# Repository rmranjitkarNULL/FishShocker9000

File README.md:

# FishShocker9000
A hardware/software system for high-voltage pulse generation and control, integrating custom PCB design, embedded firmware, and testing tools.

---

## Overview
FishShocker9000 was developed as a project to explore **embedded systems design, PCB layout, and high-voltage electronics**.  
The system combines custom hardware with **C/C++ firmware** to generate controlled electrical pulses, managed through a modular and extensible software stack.

---

## Hardware
- **Custom PCB Design** (schematics + board layouts)  
- Power delivery circuits for safe and reliable pulse generation  
- Signal conditioning and protection hardware  
- Mixed-signal layout considerations for high-voltage operation  

---

## Features
- Precise pulse generation and control  
- Configurable timing and waveform parameters  
- Modular design for hardware/firmware scalability  
- PCB + firmware tightly integrated for performance and safety  

---

## Repository Structure
FishShocker9000/
├── include/ # Header files
├── lib/ # Custom libraries
├── src/ # Firmware source code
├── test/ # Testing and validation scripts
├── pcb/ # PCB design files (schematics, layouts)
└── README.md # Project documentation

---

## Future Improvements
- Improve PCB design for efficiency and miniaturization  
- Expand safety features and protection circuitry  

---

TODO
-[ ] Redo Readme
-[ ] Make assembly guide
-[ ] [add](https://www.pjrc.com/teensy/loader.html)

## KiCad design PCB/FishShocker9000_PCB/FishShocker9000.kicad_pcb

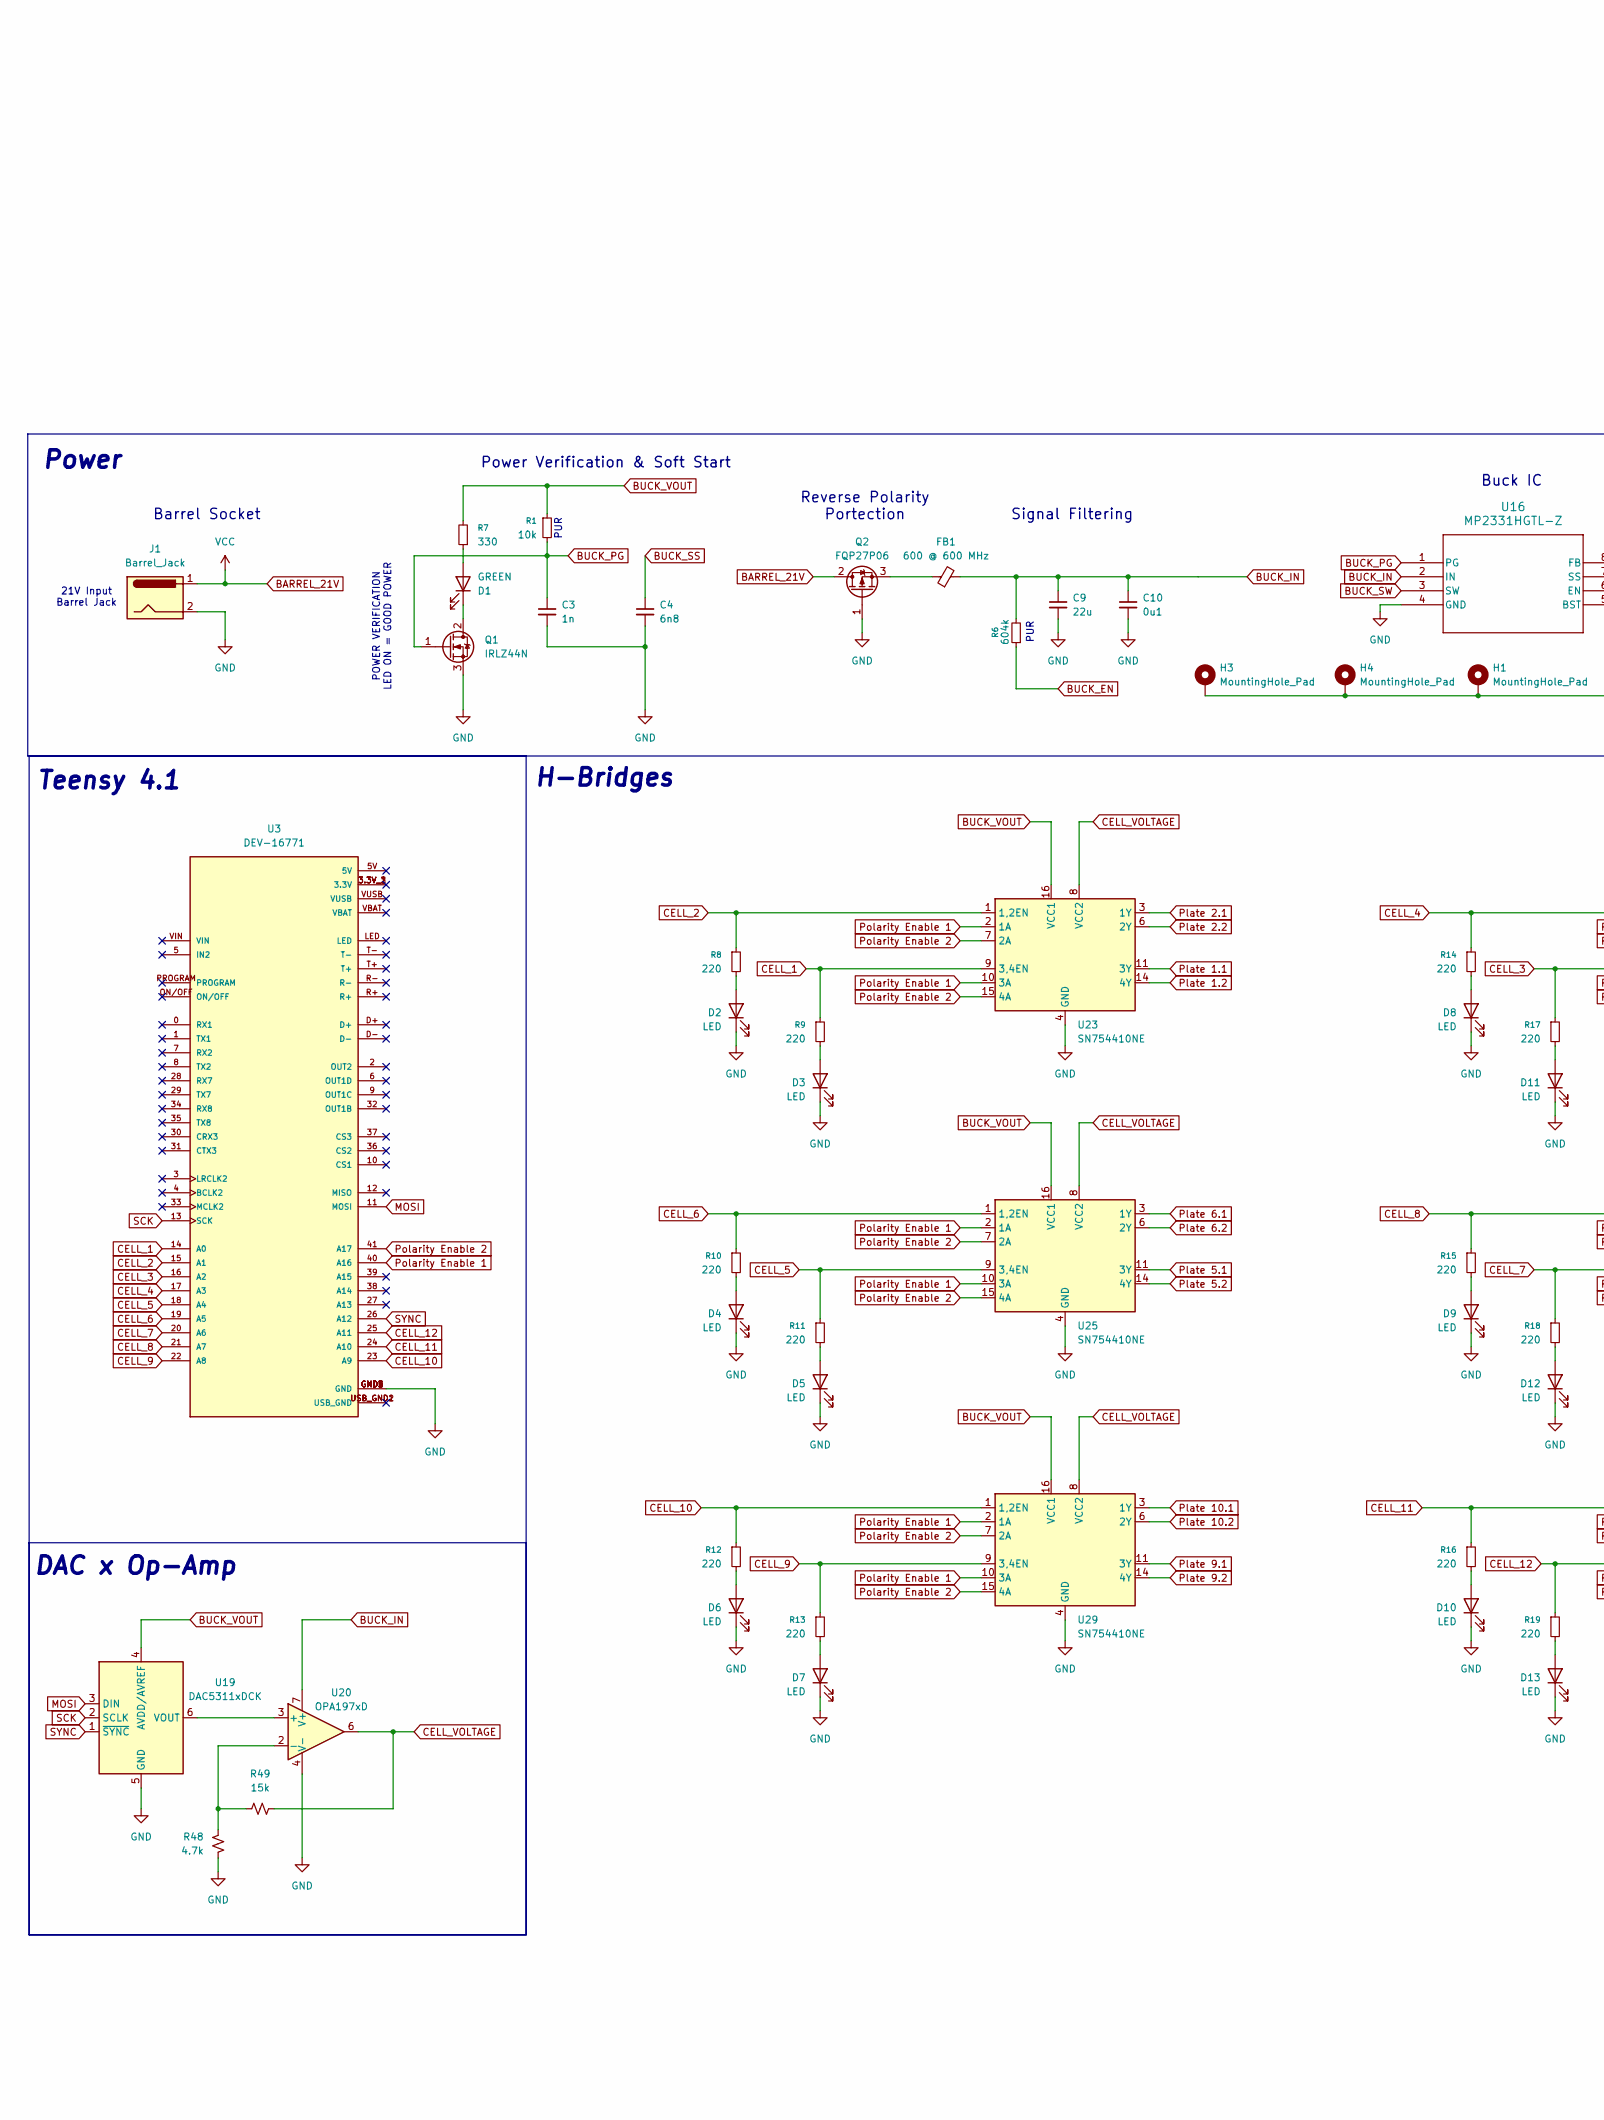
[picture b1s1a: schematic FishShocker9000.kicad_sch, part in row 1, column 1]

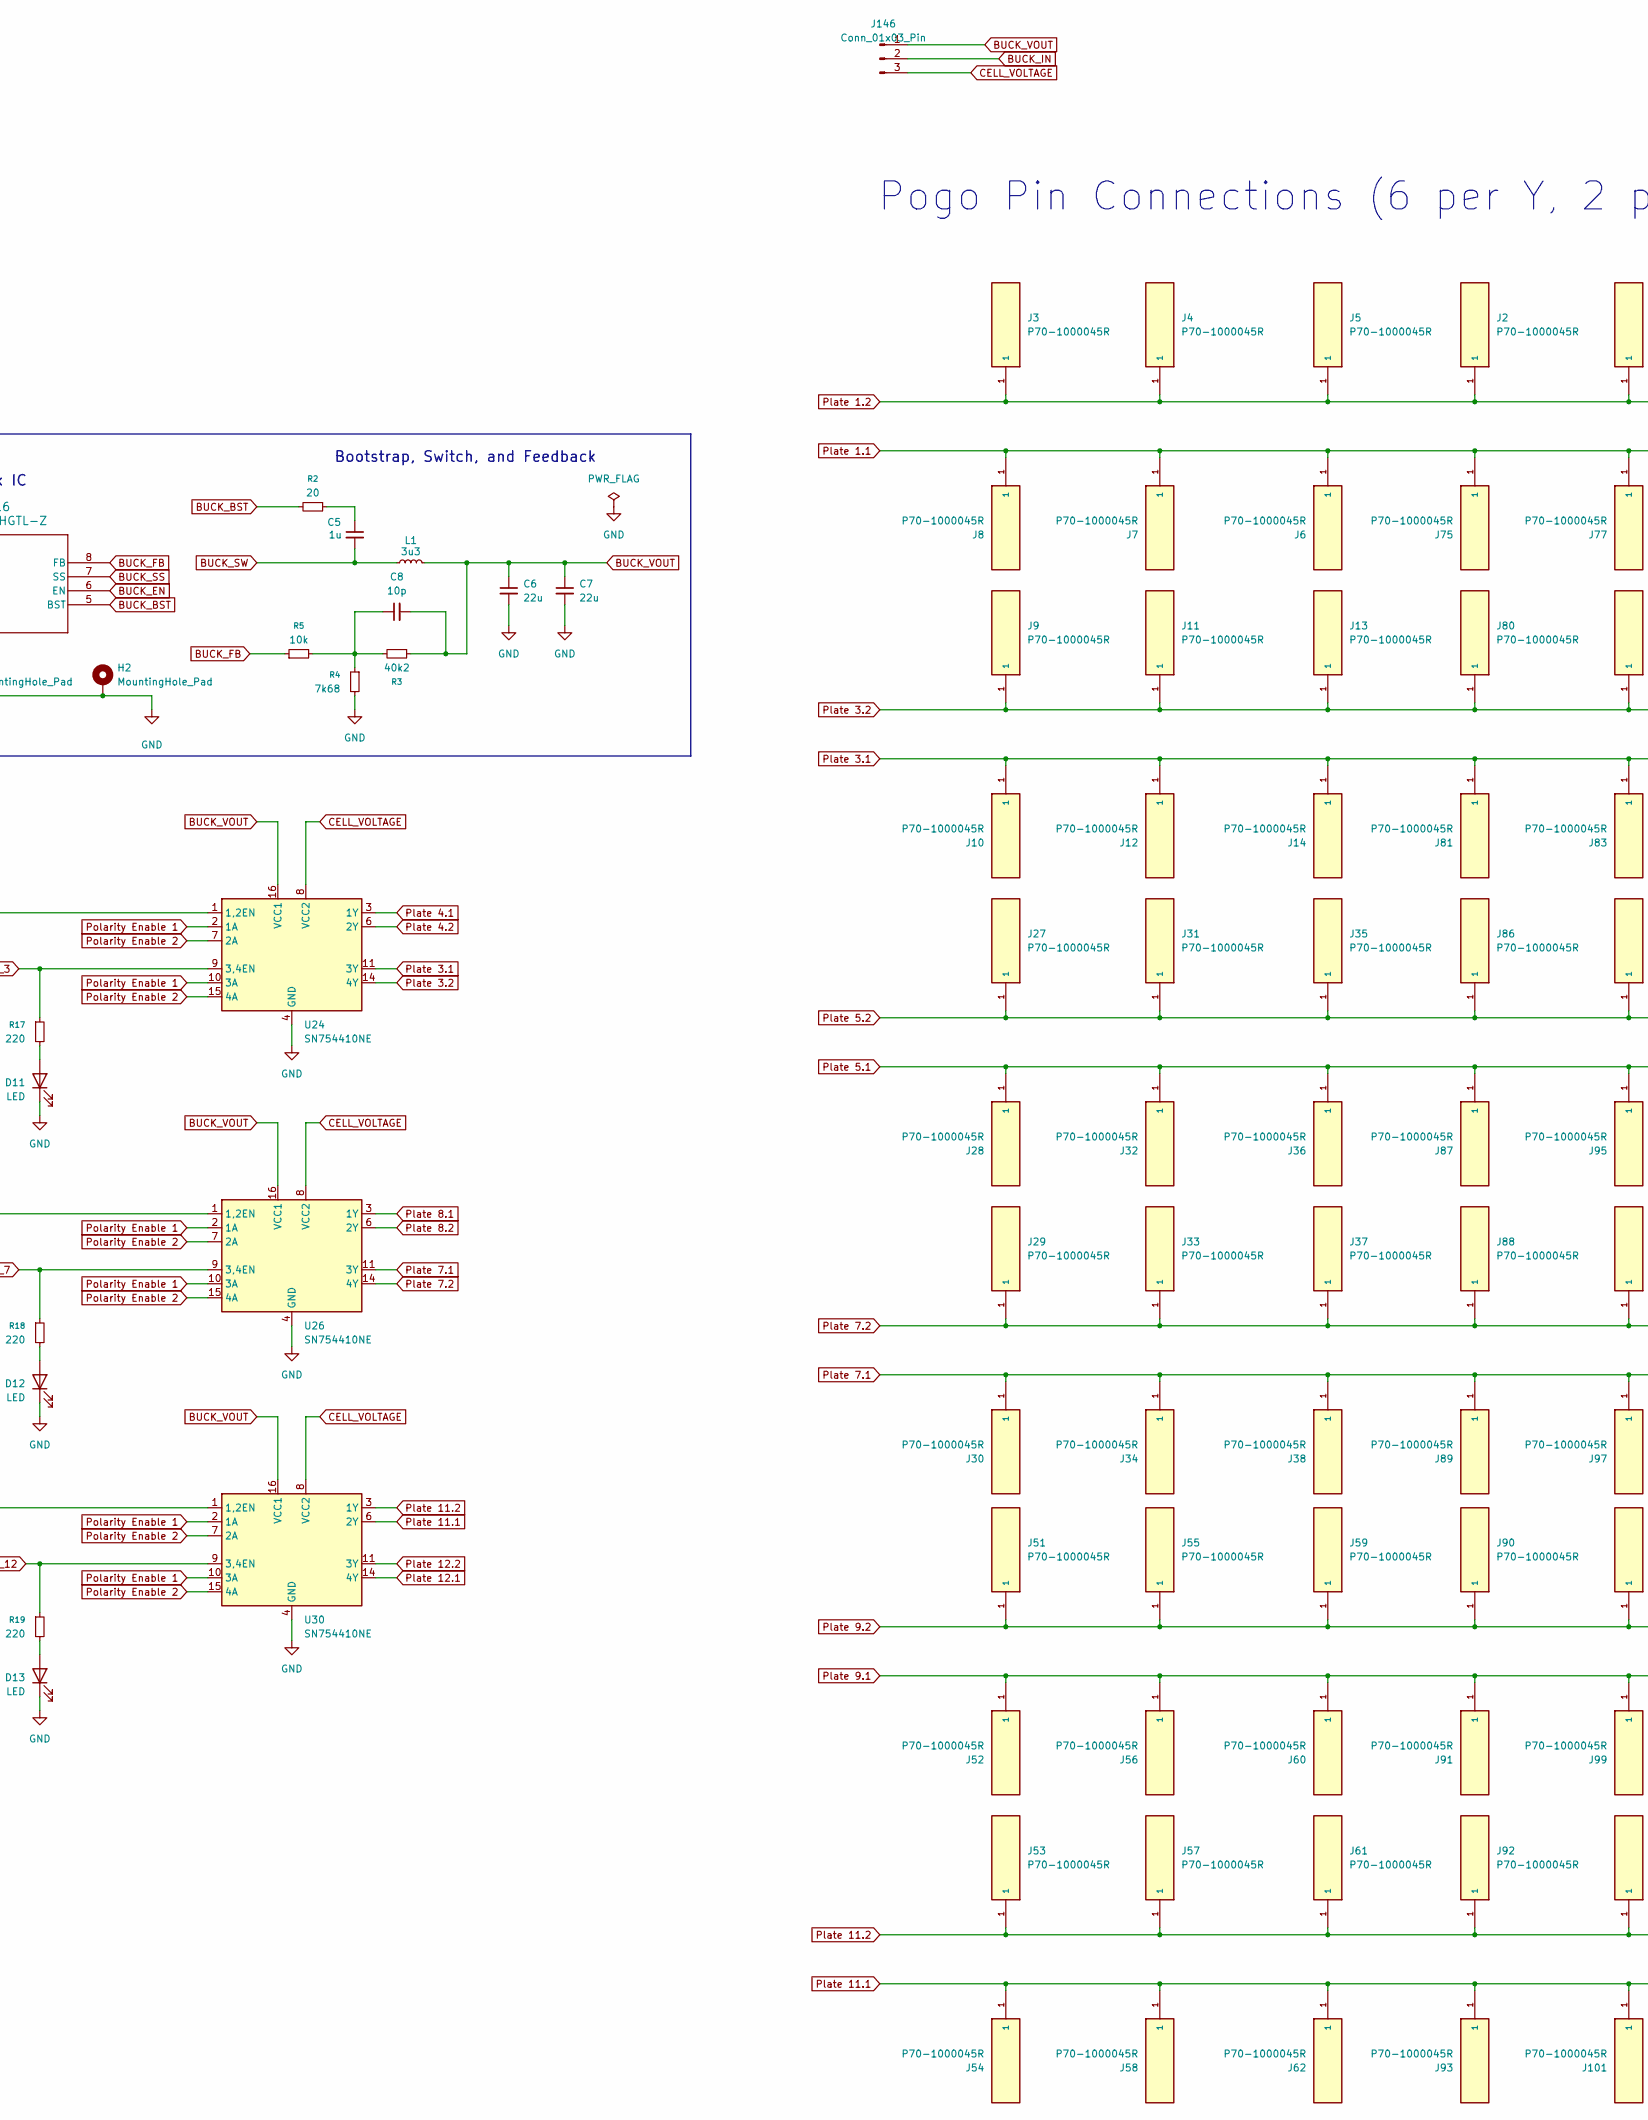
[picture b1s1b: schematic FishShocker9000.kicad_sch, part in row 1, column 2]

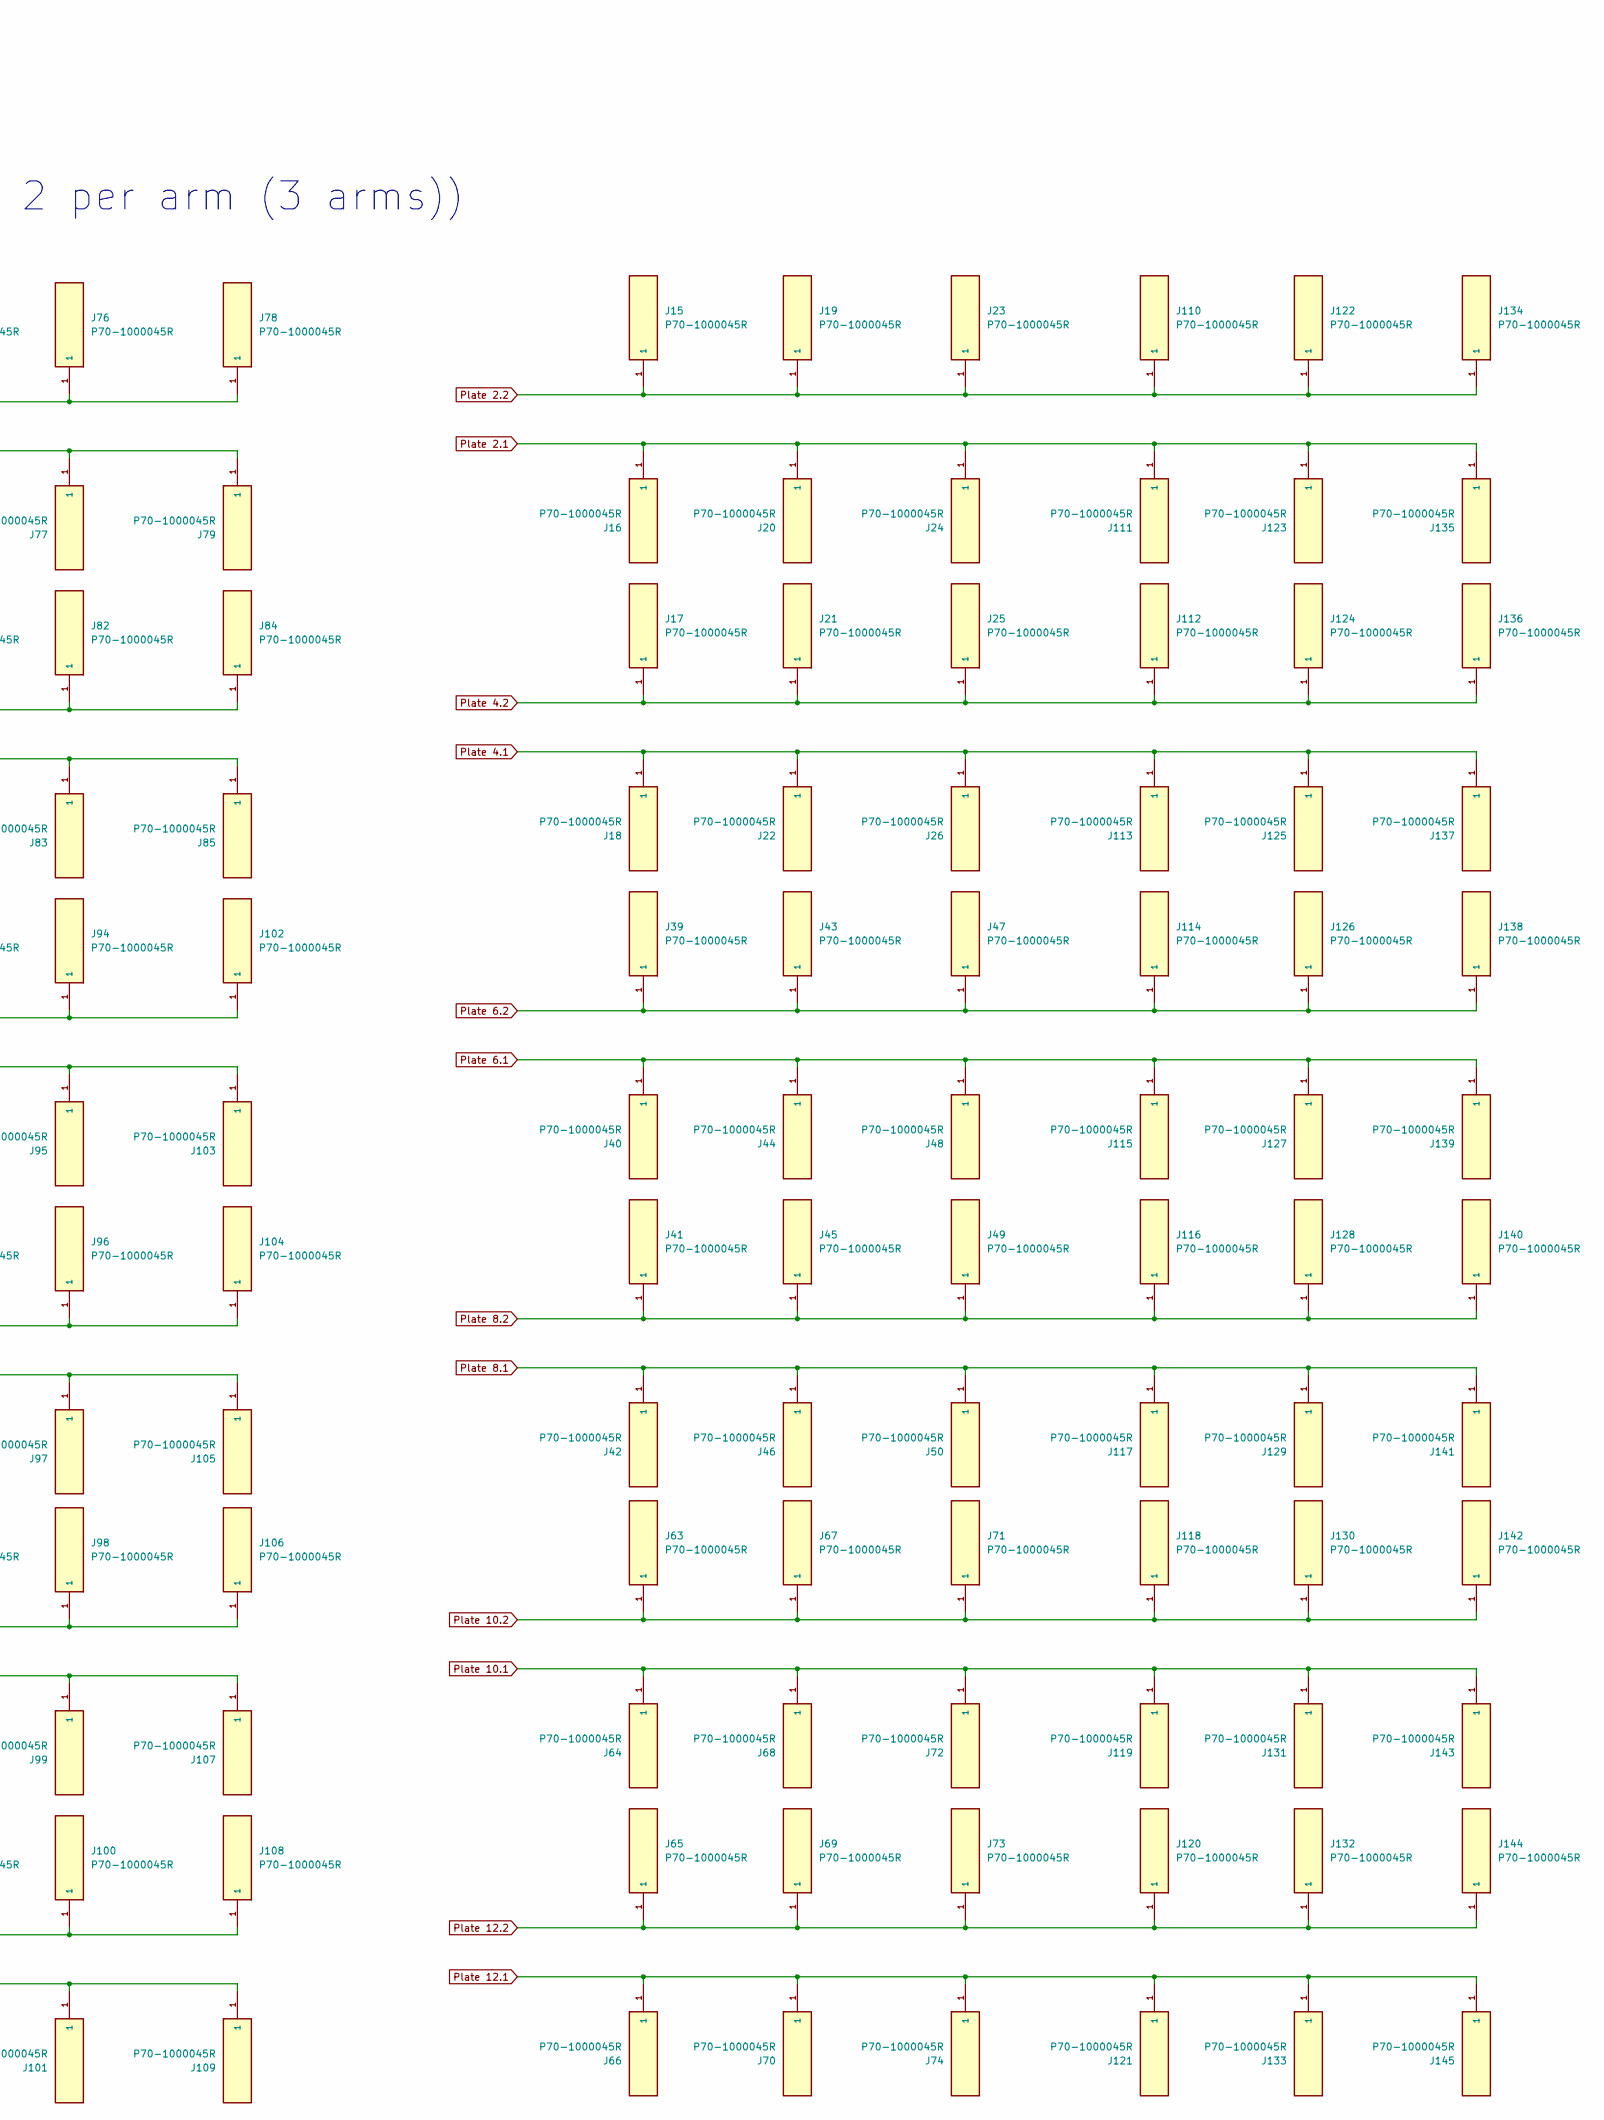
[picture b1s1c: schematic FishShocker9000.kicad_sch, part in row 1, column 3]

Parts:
C3: 1n; C_0402_1005Metric
C4: 6n8; C_0603_1608Metric
C5: 1u; C_1206_3216Metric
C6, C7, C9: 22u; C_1206_3216Metric
C8: 10p; C_0603_1608Metric
C10: 0u1; C_0603_1608Metric
D1: GREEN; LED_0805_2012Metric
D2, D3, D4, D5, D6, D7, D8, D9, D10, D11, D12, D13: LED; LED_0805_2012Metric
FB1: 600 @ 600 MHz; L_0805_2012Metric
H1, H2, H3, H4: MountingHole_Pad; MountingHole_2.2mm_M2_DIN965_Pad
J1: Barrel_Jack; BarrelJack_CLIFF_FC681465S_SMT_Horizontal
J2, J3, J4, J5, J6, J7, J8, J9, J10, J11, J12, J13, J14, J15, J16, J17, J18, J19, J20, J21, J22, J23, J24, J25, J26, J27, J28, J29, J30, J31, J32, J33, J34, J35, J36, J37, J38, J39, J40, J41, J42, J43, J44, J45, J46, J47, J48, J49, J50, J51, J52, J53, J54, J55, J56, J57, J58, J59, J60, J61, J62, J63, J64, J65, J66, J67, J68, J69, J70, J71, J72, J73, J74, J75, J76, J77, J78, J79, J80, J81, J82, J83, J84, J85, J86, J87, J88, J89, J90, J91, J92, J93, J94, J95, J96, J97, J98, J99, J100, J101, J102, J103, J104, J105, J106, J107, J108, J109, J110, J111, J112, J113, J114, J115, J116, J117, J118, J119, J120, J121, J122, J123, J124, J125, J126, J127, J128, J129, J130, J131, J132, J133, J134, J135, J136, J137, J138, J139, J140, J141, J142, J143, J144, J145: P70-1000045R; PinHeader_1x01_P2.54mm_Vertical; PARTREV 4
J146: Conn_01x03_Pin; PinHeader_1x03_P2.54mm_Vertical
L1: 3u3; L_0805_2012Metric
Q1: IRLZ44N; TO-220-3_Vertical
Q2: FQP27P06; TO-220-3_Vertical
R1, R5: 10k; R_0805_2012Metric
R2: 20; R_0805_2012Metric
R3: 40k2; R_0805_2012Metric
R4: 7k68; R_0805_2012Metric
R6: 604k; R_0805_2012Metric
R7: 330; R_0805_2012Metric
R8, R9, R10, R11, R12, R13, R14, R15, R16, R17, R18, R19: 220; R_0805_2012Metric
R48: 4.7k; R_Axial_DIN0207_L6.3mm_D2.5mm_P10.16mm_Horizontal
R49: 15k; R_Axial_DIN0207_L6.3mm_D2.5mm_P10.16mm_Horizontal
U3: DEV-16771; Teensy 4.1; PARTREV 4.1
U16: MP2331HGTL-Z; SOT583_MP2331H
U19: DAC5311xDCK; SOT-363_SC-70-6
U20: OPA197xD; SOIC-8_3.9x4.9mm_P1.27mm
U23, U24, U25, U26, U29, U30: SN754410NE; DIP-16_W7.62mm

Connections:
BARREL_21V: J1.1, Q2.2 (D)
BUCK_BST: R2.2, U16.5 (BST)
BUCK_EN: R6.1, U16.6 (EN)
BUCK_FB: R5.1, U16.8 (FB)
BUCK_IN: C9.1, C10.1, FB1.2, J146.2, R6.2, U16.2 (IN), U20.7 (V+)
BUCK_PG: C3.1, Q1.1 (G), R1.2, U16.1 (PG)
BUCK_SS: C4.1, U16.7 (SS)
BUCK_SW: C5.2, L1.1, U16.3 (SW)
BUCK_VOUT: C6.1, C7.1, C8.2, J146.1, L1.2, R1.1, R3.1, R7.2, U19.4 (AVDD/AVREF), U23.16 (VCC1), U24.16 (VCC1), U25.16 (VCC1), U26.16 (VCC1), U29.16 (VCC1), U30.16 (VCC1)
CELL_1: R9.1, U3.14 (A0), U23.9 (3,4EN)
CELL_2: R8.1, U3.15 (A1), U23.1 (1,2EN)
CELL_3: R17.1, U3.16 (A2), U24.9 (3,4EN)
CELL_4: R14.1, U3.17 (A3), U24.1 (1,2EN)
CELL_5: R11.1, U3.18 (A4), U25.9 (3,4EN)
CELL_6: R10.1, U3.19 (A5), U25.1 (1,2EN)
CELL_7: R18.1, U3.20 (A6), U26.9 (3,4EN)
CELL_8: R15.1, U3.21 (A7), U26.1 (1,2EN)
CELL_9: R13.1, U3.22 (A8), U29.9 (3,4EN)
CELL_10: R12.1, U3.23 (A9), U29.1 (1,2EN)
CELL_11: R16.1, U3.24 (A10), U30.1 (1,2EN)
CELL_12: R19.1, U3.25 (A11), U30.9 (3,4EN)
CELL_VOLTAGE: J146.3, R49.2, U20.6, U23.8 (VCC2), U24.8 (VCC2), U25.8 (VCC2), U26.8 (VCC2), U29.8 (VCC2), U30.8 (VCC2)
GND: C3.2, C4.2, C6.2, C7.2, C9.2, C10.2, D2.1 (K), D3.1 (K), D4.1 (K), D5.1 (K), D6.1 (K), D7.1 (K), D8.1 (K), D9.1 (K), D10.1 (K), D11.1 (K), D12.1 (K), D13.1 (K), H1.1, H2.1, H3.1, H4.1, J1.2, Q1.3 (S), Q2.1 (G), R4.2, R48.2, U3.GND1 (GND), U3.GND2 (GND), U3.GND3 (GND), U3.GND4 (GND), U3.GND5 (GND), U16.4 (GND), U19.5 (GND), U20.4 (V-), U23.4 (GND), U23.5 (GND), U23.12 (GND), U23.13 (GND), U24.4 (GND), U24.5 (GND), U24.12 (GND), U24.13 (GND), U25.4 (GND), U25.5 (GND), U25.12 (GND), U25.13 (GND), U26.4 (GND), U26.5 (GND), U26.12 (GND), U26.13 (GND), U29.4 (GND), U29.5 (GND), U29.12 (GND), U29.13 (GND), U30.4 (GND), U30.5 (GND), U30.12 (GND), U30.13 (GND)
MOSI: U3.11 (MOSI), U19.3 (DIN)
unnamed: C5.1, R2.1
unnamed: C8.1, R3.2, R4.1, R5.2
unnamed: D1.2 (A), R7.1
unnamed: D1.1 (K), Q1.2 (D)
unnamed: D2.2 (A), R8.2
unnamed: D3.2 (A), R9.2
unnamed: D4.2 (A), R10.2
unnamed: D5.2 (A), R11.2
unnamed: D6.2 (A), R12.2
unnamed: D7.2 (A), R13.2
unnamed: D8.2 (A), R14.2
unnamed: D9.2 (A), R15.2
unnamed: D10.2 (A), R16.2
unnamed: D11.2 (A), R17.2
unnamed: D12.2 (A), R18.2
unnamed: D13.2 (A), R19.2
unnamed: FB1.1, Q2.3 (S)
unnamed: U19.6 (VOUT), U20.3 (+)
unnamed: R48.1, R49.1, U20.2 (-)
Plate 1.1: J6.1, J7.1, J8.1, J75.1, J77.1, J79.1, U23.11 (3Y)
Plate 1.2: J2.1, J3.1, J4.1, J5.1, J76.1, J78.1, U23.14 (4Y)
Plate 2.1: J16.1, J20.1, J24.1, J111.1, J123.1, J135.1, U23.3 (1Y)
Plate 2.2: J15.1, J19.1, J23.1, J110.1, J122.1, J134.1, U23.6 (2Y)
Plate 3.1: J10.1, J12.1, J14.1, J81.1, J83.1, J85.1, U24.11 (3Y)
Plate 3.2: J9.1, J11.1, J13.1, J80.1, J82.1, J84.1, U24.14 (4Y)
Plate 4.1: J18.1, J22.1, J26.1, J113.1, J125.1, J137.1, U24.3 (1Y)
Plate 4.2: J17.1, J21.1, J25.1, J112.1, J124.1, J136.1, U24.6 (2Y)
Plate 5.1: J28.1, J32.1, J36.1, J87.1, J95.1, J103.1, U25.11 (3Y)
Plate 5.2: J27.1, J31.1, J35.1, J86.1, J94.1, J102.1, U25.14 (4Y)
Plate 6.1: J40.1, J44.1, J48.1, J115.1, J127.1, J139.1, U25.3 (1Y)
Plate 6.2: J39.1, J43.1, J47.1, J114.1, J126.1, J138.1, U25.6 (2Y)
Plate 7.1: J30.1, J34.1, J38.1, J89.1, J97.1, J105.1, U26.11 (3Y)
Plate 7.2: J29.1, J33.1, J37.1, J88.1, J96.1, J104.1, U26.14 (4Y)
Plate 8.1: J42.1, J46.1, J50.1, J117.1, J129.1, J141.1, U26.3 (1Y)
Plate 8.2: J41.1, J45.1, J49.1, J116.1, J128.1, J140.1, U26.6 (2Y)
Plate 9.1: J52.1, J56.1, J60.1, J91.1, J99.1, J107.1, U29.11 (3Y)
Plate 9.2: J51.1, J55.1, J59.1, J90.1, J98.1, J106.1, U29.14 (4Y)
Plate 10.1: J64.1, J68.1, J72.1, J119.1, J131.1, J143.1, U29.3 (1Y)
Plate 10.2: J63.1, J67.1, J71.1, J118.1, J130.1, J142.1, U29.6 (2Y)
Plate 11.1: J54.1, J58.1, J62.1, J93.1, J101.1, J109.1, U30.6 (2Y)
Plate 11.2: J53.1, J57.1, J61.1, J92.1, J100.1, J108.1, U30.3 (1Y)
Plate 12.1: J66.1, J70.1, J74.1, J121.1, J133.1, J145.1, U30.14 (4Y)
Plate 12.2: J65.1, J69.1, J73.1, J120.1, J132.1, J144.1, U30.11 (3Y)
Polarity Enable 1: U3.40 (A16), U23.2 (1A), U23.10 (3A), U24.2 (1A), U24.10 (3A), U25.2 (1A), U25.10 (3A), U26.2 (1A), U26.10 (3A), U29.2 (1A), U29.10 (3A), U30.2 (1A), U30.10 (3A)
Polarity Enable 2: U3.41 (A17), U23.7 (2A), U23.15 (4A), U24.7 (2A), U24.15 (4A), U25.7 (2A), U25.15 (4A), U26.7 (2A), U26.15 (4A), U29.7 (2A), U29.15 (4A), U30.7 (2A), U30.15 (4A)
SCK: U3.13 (SCK), U19.2 (SCLK)
SYNC: U3.26 (A12), U19.1 (~SYNC)

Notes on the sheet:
POWER VERIFICATION LED ON = GOOD POWER
Pogo Pin Connections (6 per Y, 2 per arm (3 arms))
PUR
Barrel Socket
DAC x Op-Amp
Signal Filtering
Power Verification & Soft Start
Reverse Polarity Portection
H-Bridges
Teensy 4.1
Bootstrap, Switch, and Feedback
Buck IC
21V Input Barrel Jack
Power

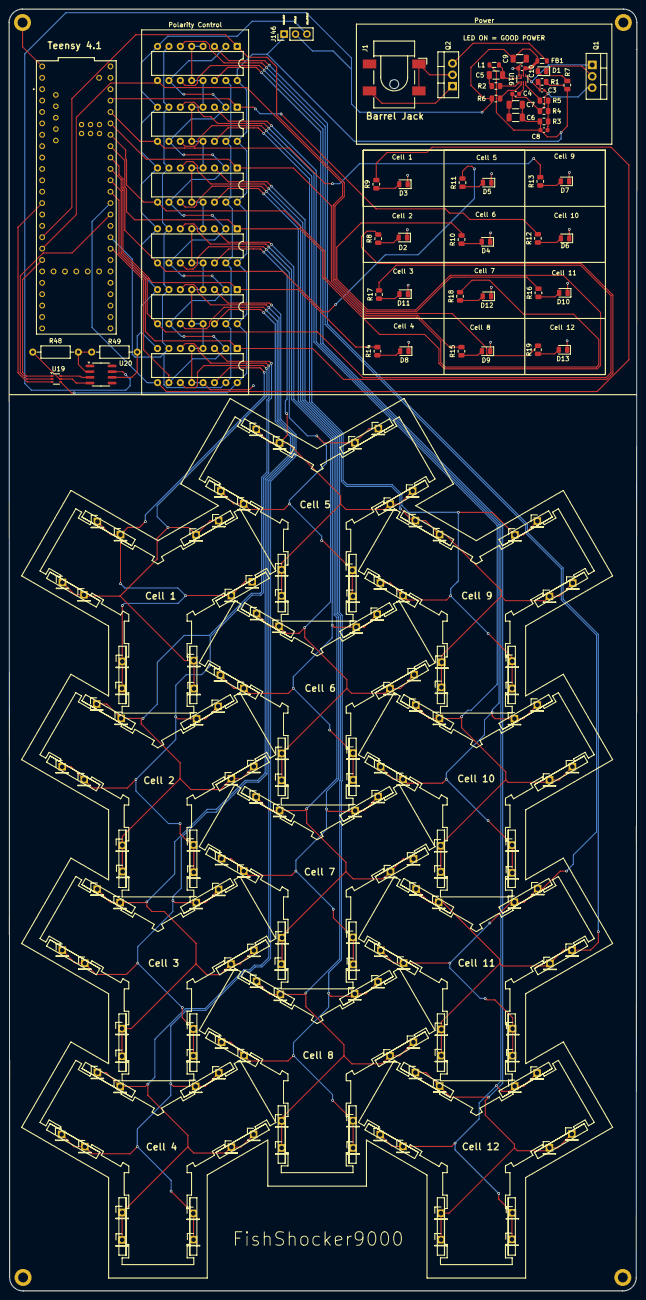
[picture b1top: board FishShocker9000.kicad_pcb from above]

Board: 2 copper layers, 140.0 x 285.9 mm, 206 parts (0 on the bottom side), 71 nets.

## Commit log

2025-06-13 Added basic implementation
2025-06-13 Added planned PCB
2025-06-13 changed the supply rail to 15v, changed op amp model to LM358
2025-06-18 made initializationc hanfges, added comments to polarity
2025-06-18 Fixed error
2025-06-18 fixed pcb with correct IC and finalized it for one cell
2025-06-26 added fifo (untested) source code to code base
2025-06-26 added cb_peek and cb_clear functions
2025-06-26 added main logic for testing
2025-06-26 Converted format to snake case for readability
2025-06-27 added serial library for testing pyurposes
2025-07-01 Added barebones component to the mechanics (No Values)
2025-07-01 made syntax comment changes
2025-07-01 Remove backups folder from tracking
2025-07-01 Finalized Power Schematic and Op amp connections
2025-07-02 Changes to Gitignore
2025-07-10 Fixed serial data issue
2025-07-10 Verified FIFO is working as intended
2025-07-14 Changed timing of shocking to be more applicable to each cell (UNTESTD)
2025-07-15 Added values to passive components. Need to add various footprints and change pmos transistor to FQP47P06.
2025-07-16 changed some values for the PCB
2025-07-16 Added CAN Bus Tranciever and Pogo Pins
2025-07-16 Made general layout for PCB
2025-07-17 routed PCB except for GND and Pogo Pins
2025-07-18 New draft of final PCB layout
2025-07-18 Changed Layout to eb more clean
2025-07-22 Made changes to the SChematic. Now use DAC instead of sevberal op amps
2025-07-22 Shock.cpp changes
2025-07-23 added various items to the schematic
2025-07-23 Made Changes but not complete PCB. Gonna reformat
2025-07-23 Rerouted PCB layout to actually fit and work. Need to connect Pogo Pins
2025-07-23 Fixed some other issues. Pogo Pins still not connected
2025-07-25 Placed Pogo Pins
2025-07-25 Saved Pogo Pin Changes
2025-07-25 Routed all plates. Messy, gonna try and reroute to be neater
2025-07-25 Much cleaner Route. Finalized all changes for the final PCB
2025-07-28 Fixed Teensy being double powered
2025-07-28 Added testing headers
2025-07-28 removed USB gnd
2025-07-28 Fixed Corruption issues
2025-07-28 Fixed more corruption
2025-07-30 Changed pogo pin footprints to connector, fixed routing, removed ferrite bead
2025-08-14 Fixed some syntax errors. Verifying New teensy pins
2025-08-14 vscode settings json change
2025-08-14 Stup[id vscode setting
2025-08-14 Fixed corrupted PCB
2025-08-14 Fixed corrupted PCB again
2025-08-14 Verified Cell Pin connections. Need to fix sender.py to toggle Cell pins
2025-08-15 Issued syntax chanfges
2025-08-15 Implemented DAC FUnctions (Untested)
2025-08-15 added function prototype and definitions
2025-08-15 Forgot to add return parameter
2025-08-15 Moved Code format to a different location
2025-08-15 Fixed laggy git?
2025-08-18 Vscode setting
2025-08-18 Improved timing for shock
2025-08-18 Added DAC functions to main for testing
2025-08-18 Fixed syntax. Testing DAC
2025-08-18 Vscode settings.json change
2025-08-19 DAC Testing
2025-08-19 Fixed SPI line issue: DO NOT USE THE BUILT IN LED NO MATTER WHAT
2025-08-19 I hate LEDs
2025-08-20 Changed TODO and Gitignore
2025-10-15 Change platformio ini
2025-10-16 Added timer test
2025-10-17 DAC values are close enough. Weird offset error, but its close to the desired values.
2026-01-30 Final Metal sheets work well
2026-01-30 changed to actal params
2026-01-30 Found good shock parameters
2026-02-03 Fish shockeed with some QOL changes needed
2026-05-06 remade git ignore
2026-05-06 Remove venv from repository
2026-05-06 Remove local VS Code settings from repository
2026-05-06 Update README to remove emojis and License section
    Removed emoji from Future Improvements section and License.
2026-05-06 Remove software development details from README
    Removed software section detailing development environment and structure.
2026-05-06 new file structure
2026-05-06 added extensions.json to gitignore
2026-05-06 removed extensions.json from git ignore
